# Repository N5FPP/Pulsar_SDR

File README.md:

Pulsar SDR
==========

Altera Cyclone FPGA Code to implement a Software Defined Radio

Developed for Tayloe detector and DE0 Nano dev board
Eventually will be migrated to a direct sampling design

## TO DO

In something of a priority order.

### Tests

* Receive
    * Save quadrature sampling data for post-processing with GNU Radio
    * Streaming receive over Ethernet

* Transmit
    * Block transmit with DAC direct out
    * Streaming transmit over Ethernet

### Hardware

* Decide on and purchase new FPGA dev board
* Layout, manufacture and build LT2208 board
* Qualify noise performance of RX signal chain
* Qualify noise performance of DAC (does this need a spectrum analyzer?)
* Layout, manufacture and build TxDAC board
* Construct HF amplifier (10W with cheap power FETs ?)
* Package in some kind of nice case
* Do something hella cool (Summits on the Air?)
* Build down-converter
* Do additional hella cool things (moon bounce?)

### FPGA/HDL

* Learn how to work with FIFOs
* Create PHY interface compatible with [UHD](http://code.ettus.com/redmine/ettus/projects/uhd/wiki)
* ADC interface (LT2208)
* Down sampling filters
* Glue logic and control circuits

### Software/GNU Radio

* Experiment with demodulating simple voice/data modes (AM, SSB, RTTY, PSK)
* Determine if GNU radio based system or SDR#/HDSDR/linrad
* Learn how to use UHD driver

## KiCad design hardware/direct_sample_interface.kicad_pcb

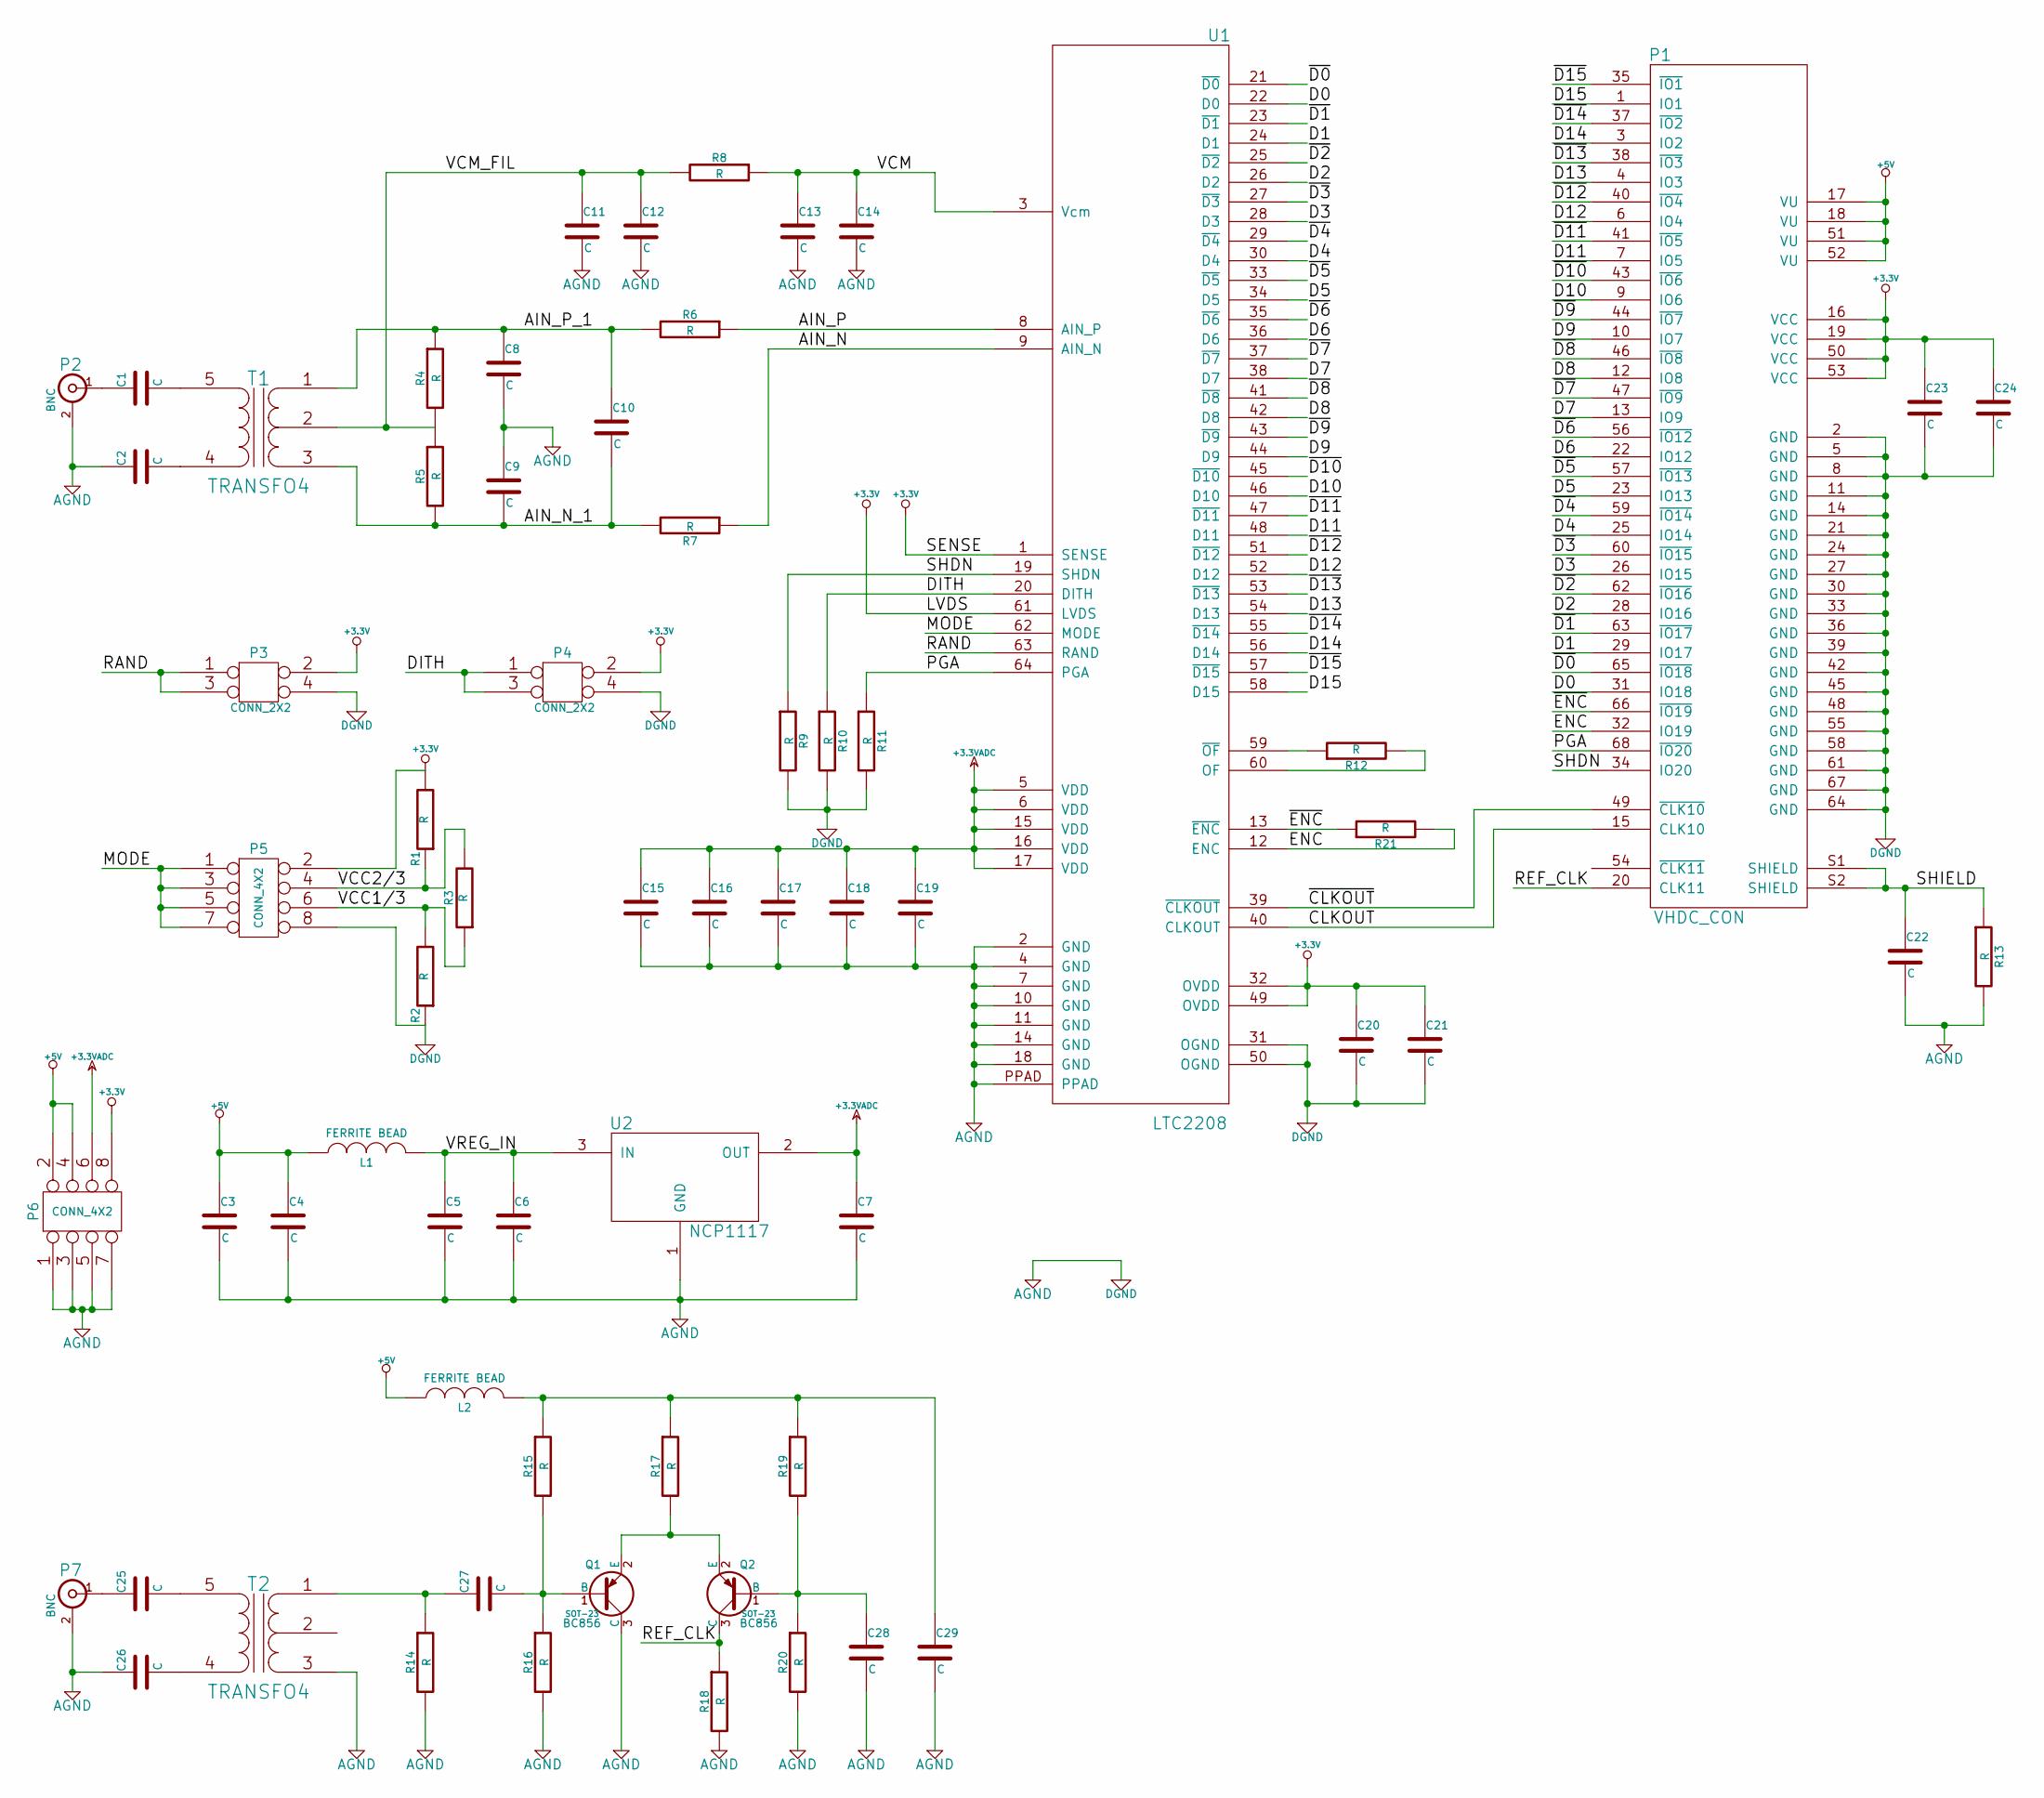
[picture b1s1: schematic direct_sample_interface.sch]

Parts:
C1, C2, C3, C4, C5, C6, C7, C8, C9, C10, C11, C12, C13, C14, C15, C16, C17, C18, C19, C20, C21, C22, C23, C24, C25, C26, C27, C28, C29: C
L1, L2: FERRITE BEAD
P1: VHDC_CON
P2, P7: BNC
P3, P4: CONN_2X2
P5, P6: CONN_4X2
Q1, Q2: BC856; SOT-23
R1, R2, R3, R4, R5, R6, R7, R8, R9, R10, R11, R12, R13, R14, R15, R16, R17, R18, R19, R20, R21: R
T1, T2: TRANSFO4
U1: LTC2208
U2: NCP1117

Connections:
+3.3V: C20.1, C21.1, C23.1, C24.1, P1.16 (VCC), P1.19 (VCC), P1.50 (VCC), P1.53 (VCC), P3.2, P4.2, P5.2, P6.8, R1.2, U1.1 (SENSE), U1.32 (OVDD), U1.49 (OVDD), U1.61 (LVDS)
+3.3VADC: C7.1, C15.1, C16.1, C17.1, C18.1, C19.1, P6.6, U1.5 (VDD), U1.6 (VDD), U1.15 (VDD), U1.16 (VDD), U1.17 (VDD), U2.2 (OUT)
+5V: C3.1, C4.1, L1.1, L2.1, P1.17 (VU), P1.18 (VU), P1.51 (VU), P1.52 (VU), P6.2, P6.4
/AIN_N: R7.1, U1.9 (AIN_N)
/AIN_N_1: C9.2, C10.2, R5.2, R7.2, T1.3 (PR2)
/AIN_P: R6.1, U1.8 (AIN_P)
/AIN_P_1: C8.1, C10.1, R4.1, R6.2, T1.1 (PR1)
/CLKOUT: P1.15 (CLK10), U1.40 (CLKOUT)
/D0: P1.31 (IO18), U1.22 (D0)
/D1: P1.29 (IO17), U1.24 (D1)
/D2: P1.28 (IO16), U1.26 (D2)
/D3: P1.26 (IO15), U1.28 (D3)
/D4: P1.25 (IO14), U1.30 (D4)
/D5: P1.23 (IO13), U1.34 (D5)
/D6: P1.22 (IO12), U1.36 (D6)
/D7: P1.13 (IO9), U1.38 (D7)
/D8: P1.12 (IO8), U1.42 (D8)
/D9: P1.10 (IO7), U1.44 (D9)
/D10: P1.9 (IO6), U1.46 (D10)
/D11: P1.7 (IO5), U1.48 (D11)
/D12: P1.6 (IO4), U1.52 (D12)
/D13: P1.4 (IO3), U1.54 (D13)
/D14: P1.3 (IO2), U1.56 (D14)
/D15: P1.1 (IO1), U1.58 (D15)
/DITH: P4.1, P4.3, R10.1, U1.20 (DITH)
/ENC: P1.32 (IO19), R21.2, U1.12 (ENC)
/MODE: P5.1, P5.3, P5.5, P5.7, U1.62 (MODE)
/PGA: P1.68 (~IO20), R11.1, U1.64 (PGA)
/RAND: P3.1, P3.3, U1.63 (RAND)
/REF_CLK: P1.20 (CLK11), Q2.3 (C), R18.1
/SHDN: P1.34 (IO20), R9.1, U1.19 (SHDN)
/SHIELD: C22.1, P1.S1 (SHIELD), P1.S2 (SHIELD), R13.1
/VCC1/3: P5.6, R2.2, R3.1
/VCC2/3: P5.4, R1.1, R3.2
/VCM: C13.1, C14.1, R8.1, U1.3 (Vcm)
/VCM_FIL: C11.1, C12.1, R4.2, R5.1, R8.2, T1.2 (PM)
/VREG_IN: C5.1, C6.1, L1.2, U2.3 (IN)
/~CLKOUT: P1.49 (~CLK10), U1.39 (~CLKOUT)
/~D0: P1.65 (~IO18), U1.21 (~D0)
/~D1: P1.63 (~IO17), U1.23 (~D1)
/~D2: P1.62 (~IO16), U1.25 (~D2)
/~D3: P1.60 (~IO15), U1.27 (~D3)
/~D4: P1.59 (~IO14), U1.29 (~D4)
/~D5: P1.57 (~IO13), U1.33 (~D5)
/~D6: P1.56 (~IO12), U1.35 (~D6)
/~D7: P1.47 (~IO9), U1.37 (~D7)
/~D8: P1.46 (~IO8), U1.41 (~D8)
/~D9: P1.44 (~IO7), U1.43 (~D9)
/~D10: P1.43 (~IO6), U1.45 (~D10)
/~D11: P1.41 (~IO5), U1.47 (~D11)
/~D12: P1.40 (~IO4), U1.51 (~D12)
/~D13: P1.38 (~IO3), U1.53 (~D13)
/~D14: P1.37 (~IO2), U1.55 (~D14)
/~D15: P1.35 (~IO1), U1.57 (~D15)
/~ENC: P1.66 (~IO19), R21.1, U1.13 (~ENC)
AGND: C2.1, C3.2, C4.2, C5.2, C6.2, C7.2, C8.2, C9.1, C11.2, C12.2, C13.2, C14.2, C15.2, C16.2, C17.2, C18.2, C19.2, C20.2, C21.2, C22.2, C23.2, C24.2, C26.1, C28.2, C29.2, P1.2 (GND), P1.5 (GND), P1.8 (GND), P1.11 (GND), P1.14 (GND), P1.21 (GND), P1.24 (GND), P1.27 (GND), P1.30 (GND), P1.33 (GND), P1.36 (GND), P1.39 (GND), P1.42 (GND), P1.45 (GND), P1.48 (GND), P1.55 (GND), P1.58 (GND), P1.61 (GND), P1.64 (GND), P1.67 (GND), P2.2 (Ext), P3.4, P4.4, P5.8, P6.1, P6.3, P6.5, P6.7, P7.2 (Ext), Q1.3 (C), R2.1, R9.2, R10.2, R11.2, R13.2, R14.2, R16.2, R18.2, R20.2, T2.3 (PR2), U1.2 (GND), U1.4 (GND), U1.7 (GND), U1.10 (GND), U1.11 (GND), U1.14 (GND), U1.18 (GND), U1.31 (OGND), U1.50 (OGND), U1.PPAD, U2.1 (GND)
unnamed: R12.2, U1.60 (OF)
unnamed: R12.1, U1.59 (~OF)
unnamed: C27.1, R14.1, T2.1 (PR1)
unnamed: C29.1, L2.2, R15.1, R17.1, R19.1
unnamed: C27.2, Q1.1 (B), R15.2, R16.1
unnamed: C26.2, T2.4 (S1)
unnamed: C25.1, P7.1 (In)
unnamed: C25.2, T2.5 (S2)
unnamed: Q1.2 (E), Q2.2 (E), R17.2
unnamed: C28.1, Q2.1 (B), R19.2, R20.1
unnamed: C1.1, P2.1 (In)
unnamed: C2.2, T1.4 (S1)
unnamed: C1.2, T1.5 (S2)

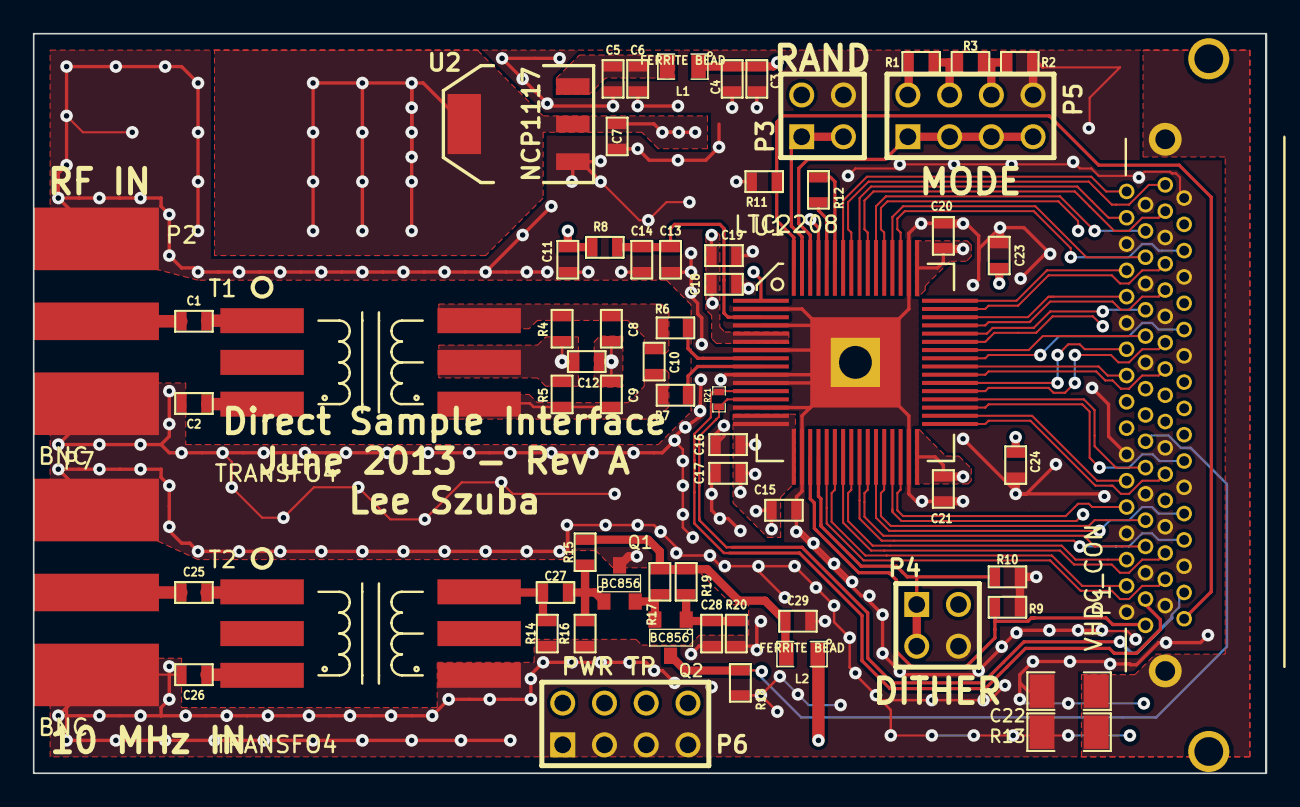
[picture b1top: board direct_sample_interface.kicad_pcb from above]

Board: 4 copper layers, 75.0 x 45.0 mm, 65 parts (0 on the bottom side), 69 nets.

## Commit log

2012-05-23 Added project files.
2012-06-19 First major edit
2012-06-20 Moved PLL reconfig and PLL setup code to seprate module.
2012-06-21 Added a FIFO module to be used later and continued refactoring the PLL Code
2012-06-23 Removed unused files and continued refactoring PLL setup.
2012-06-29 Modified some of the PLL code, currently testing hardware.
2012-07-07 Added a vga output module, so far with simple text display
2012-08-31 Deleted excess files
2013-01-09 Major update, attempting to simplify version control by removing unneeded files.
2013-01-09 Removed some files.
2013-01-09 Removed config and project files
2013-01-09 Removing unneeded files
2013-01-09 More file deletions
2013-01-09 More file removals
2013-06-03 Add to do list. Experiment with DDS.
2013-06-21 Added/finished hardware designs for direct sample PCB
